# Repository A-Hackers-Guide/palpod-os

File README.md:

# HearthOS

> The software layer of Hearth — a $95k fully-offline luxury home AI and media
> server. This repository provides the orchestration scaffolding: everything a
> single Jetson AGX Orin dev kit needs to boot into a working Pod after one
> `install.sh`.

---

## What this is

HearthOS is the **base platform**. It brings up:

- Media services (Plex, Jellyfin, Audiobookshelf)
- Live-TV proxy (xTeVe → M3U/EPG into Plex & Jellyfin as first-class channels)
- Game & desktop streaming (Sunshine, GPU-accelerated, Moonlight-compatible)
- Headless Steam (Steam Big Picture streamed to any Moonlight client — never to
  the Sphere face)
- Remote Desktop — RustDesk self-hosted (rendezvous + relay) so the Pod can
  view and drive your other machines with your permission; AnyDesk is
  available as an opt-in `--profile anydesk` alternative
- A Postgres 16 database for the `pal-web` control app
- A reverse proxy (Traefik) with LAN-local TLS on `*.palpod.local`
- Reference mount points for the three sibling repos:
  `pal-web`, `pal-voice`, `pal-face`

MVP hardware: **one NVIDIA Jetson AGX Orin 64GB Developer Kit** running
Ubuntu 22.04 aarch64.

Production hardware (future): a cluster of 10× Jetson Orin NX + 10× Ryzen
AI 9 HX 370 nodes on TrueNAS SCALE with 5 TB ECC DDR5 and 35 TB NVMe JBOD.
The compose file here is the **development target**; the production target is
TrueNAS's Kubernetes app catalog (see [`docs/ARCHITECTURE.md`](docs/ARCHITECTURE.md)).

---

## Remote Desktop

The Pod can view and drive your other machines — Macs, PCs, iPhones,
Androids — through a self-hosted RustDesk stack. The rendezvous server
(`hbbs`) handles peer discovery and the relay (`hbbr`) forwards traffic when
a direct LAN path isn't available. Both run on the Pod. **No third-party
server ever touches your streams**, and the X25519 keypair used to
authenticate peers is generated during `install.sh` and never leaves the box.

Typical use:

- *"Hey Hearth, show me the office Mac"* → Pod pulls up a live view of that
  machine on the TV you're near (or any Moonlight extender).
- *"Hey Hearth, click the send button on my laptop"* → Pod drives the mouse and
  keyboard on the remote machine — only for devices you've explicitly
  granted **AI control** to.
- The pal-web UI lists every registered device, opens a session, and shows
  session history from the `remote_sessions` Postgres table.

### Setup flow

1. Install the RustDesk client on the machine you want to reach
   (macOS, Windows, Linux, iOS, Android — all supported by upstream).
2. On the Pod, run `scripts/pair-remote-device.sh` — it prints a one-time
   pairing token and the Pod's rendezvous address.
3. Paste both into the RustDesk client's "ID Server" field. Approve the
   pairing dialog that pops up in pal-web.
4. The device shows up under **Settings → Remote Devices** in pal-web.

### Permission model

- **Default: view-only.** Voice requests like "show me…" work out of the box
  for any paired device.
- **AI control is opt-in per device.** In pal-web, toggle *Allow AI control*
  on the device card. Without this flag the click/type/scroll endpoints
  return 403 even to an authenticated Pod session.
- **Every session is logged.** Start time, end time, initiator (voice / web
  / API), input events for AI-driven sessions, all recorded in
  `remote_sessions`. Revoke a device from the same page — its auth token is
  destroyed and any live session is torn down.

### AnyDesk alternative

Some users prefer AnyDesk's commercial client. The compose file ships an
AnyDesk service behind a `docker compose` profile, disabled by default.
Opt in with:

```bash
docker compose --profile anydesk up -d
```

You'll be prompted to accept the AnyDesk EULA on first launch. RustDesk and
AnyDesk can run side-by-side; pal-web treats them as two backends behind the
same "Remote Devices" list.

---

## Install (Ubuntu 22.04, Jetson AGX Orin)

```bash
git clone https://github.com/palpod/palpod-os.git
cd palpod-os
./install.sh
```

`install.sh` will:

1. Detect the NVIDIA GPU and install the NVIDIA Container Toolkit.
2. Install Docker Engine and the `docker compose` plugin.
3. Copy `.env.example` → `.env` and prompt you for the missing values.
4. Pull every image referenced in `docker-compose.yml`.
5. Run `scripts/first-boot.sh` to create ZFS datasets (if TrueNAS is present)
   or plain directories under `/var/lib/palpod` (Ubuntu default).
6. `docker compose up -d` — and print the URLs to open in your browser.

---

## Architecture

```mermaid
flowchart LR
    subgraph LAN["Home LAN — nothing leaves the house"]
        subgraph Pod["Hearth (Jetson AGX Orin, MVP)"]
            direction TB
            Traefik["Traefik<br/>TLS + subdomains"]
            subgraph Media["Media Stack"]
                Plex
                Jellyfin
                ABS["Audiobookshelf"]
                xTeVe
            end
            subgraph Streaming["Game/Desktop Streaming"]
                Sunshine
                Steam["Headless Steam"]
            end
            subgraph Custom["Custom Hearth services (sibling repos)"]
                PalWeb["pal-web<br/>(unified control app)"]
                PalVoice["pal-voice<br/>(LLM + STT + TTS + wake)"]
                PalFace["pal-face<br/>(Pygame Sphere face)"]
            end
            Postgres[(Postgres 16)]
            PalWeb --> Postgres
            PalVoice --> Postgres
            Traefik --> Plex
            Traefik --> Jellyfin
            Traefik --> ABS
            Traefik --> PalWeb
            xTeVe -.M3U/EPG.-> Plex
            xTeVe -.M3U/EPG.-> Jellyfin
            Steam --Big Picture--> Sunshine
        end
        Moonlight["Moonlight clients<br/>(TV, tablet, phone)"]
        Sphere["Sphere face display<br/>(HDMI-attached)"]
        Extender1["Extender node<br/>(Ryzen AI or Orin NX)"]
        Sunshine <---> Moonlight
        PalFace --HDMI--> Sphere
        Pod <-.mDNS pairing.-> Extender1
    end
```

## Service ports

| Service          | Container         | LAN URL (via Traefik)              | Direct port  | Notes                             |
|------------------|-------------------|------------------------------------|--------------|-----------------------------------|
| Plex             | `plex`            | `https://plex.palpod.local`        | `32400`      | Owner claim token needed on init  |
| Jellyfin         | `jellyfin`        | `https://jelly.palpod.local`       | `8096`       | HW transcode via `/dev/nvhost*`   |
| Audiobookshelf   | `audiobookshelf`  | `https://books.palpod.local`       | `13378`      |                                   |
| xTeVe            | `xteve`           | `https://xteve.palpod.local`       | `34400`      | Feeds Plex & Jellyfin             |
| Sunshine         | `sunshine`        | `https://sunshine.palpod.local`    | `47990`      | Web UI. Stream on 47984–48010     |
| Steam (headless) | `steam-headless`  | (via Sunshine)                     | n/a          | Never routed to Sphere            |
| Postgres 16      | `postgres`        | (internal only)                    | `5432`       | Backing store for `pal-web`       |
| Traefik          | `traefik`         | `https://traefik.palpod.local`     | `80/443`     | Dashboard on `:8080` (internal)   |
| pal-web          | `pal-web`         | `https://pod.palpod.local`         | `3000`       | Sibling repo, code-mounted        |
| pal-voice        | `pal-voice`       | (internal gRPC)                    | `50051`      | Sibling repo, code-mounted        |
| pal-face         | `pal-face`        | (HDMI output, no port)             | n/a          | Sibling repo, code-mounted        |
| RustDesk hbbs    | `rustdesk-hbbs`   | (LAN-direct)                       | `21115-21116`| Rendezvous / ID server            |
| RustDesk hbbr    | `rustdesk-hbbr`   | (LAN-direct)                       | `21117`      | Relay server (fallback path)      |
| AnyDesk (opt-in) | `anydesk`         | (LAN-direct)                       | n/a          | Off by default; `--profile anydesk` |

---

## Known limitations (MVP)

This scaffolding is intentionally opinionated toward the **single-Jetson developer
kit**. In particular:

- **No Kubernetes.** Production Pods run on TrueNAS SCALE and are deployed via
  its Kubernetes app catalog. Porting each service is straightforward but out of
  scope here. See [`docs/ARCHITECTURE.md`](docs/ARCHITECTURE.md) §Production.
- **No ZFS by default.** On Ubuntu, everything lives under `/var/lib/palpod/`.
  If ZFS is detected, the first-boot script will offer to create datasets.
- **No hardware failover.** The compose stack is single-node. Extender pairing
  is defined (see [`docs/EXTENDER_PAIRING.md`](docs/EXTENDER_PAIRING.md)) but
  role reassignment on primary loss is a v1.1 feature.
- **Sunshine + Steam are Linux-native.** On the Jetson (aarch64) Steam runs
  under Proton via Box64 emulation and only a subset of the library is playable.
  Real production nodes use the Ryzen AI x86 servers for gaming.
- **TLS on `*.palpod.local` is a self-signed root** installed on the LAN.
  Public certs are out of scope — nothing here should touch the public internet.

---

## Repo layout

```
palpod-os/
├── docker-compose.yml       # THE compose file
├── install.sh / update.sh / uninstall.sh
├── configs/                 # Per-service config (traefik, xteve, sunshine, …)
├── systemd/                 # Boot units
├── scripts/                 # first-boot, extender-pair, media-import
└── docs/                    # Architecture, install, extender protocol, security, backup
```

## Sibling repos (built in parallel by the other teams)

- `pal-web`   — Next.js unified control app; mounted at `../pal-web`
- `pal-voice` — LLM + Whisper STT + Piper TTS + openWakeWord; mounted at `../pal-voice`
- `pal-face`  — Pygame Sphere face renderer; mounted at `../pal-face`

Update these paths in `.env` if your checkout layout differs.

---

## License

Apache 2.0 — see [LICENSE](LICENSE).

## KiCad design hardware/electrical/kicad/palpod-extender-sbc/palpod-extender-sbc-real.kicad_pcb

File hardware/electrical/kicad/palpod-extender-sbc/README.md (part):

# Hearth Ember SBC - KiCad Project

Thin-client single-board computer for the half-scale Hearth extender: a
Rockchip RK3588 octa-core SoC (quad A76 + quad A55, 6 TOPS NPU) hosts 8 GB
LPDDR5-6400 (Samsung K3LKBFB0EM-MGCP), 128 GB Kingston EMMC128G-M525 eMMC 5.1,
a Realtek RTL8852BE Wi-Fi 6E + BT 5.3 module on M.2 A+E 2230, an RTL8125BG
2.5 GbE PHY, a Cirrus CS43198 stereo DAC feeding a TI TPA3255 315 W class-D
amp for the extender's soundbar + mini-sub, HDMI 2.1 out to the TV, MIPI DSI-2
to the 3.5" levitating orb OLED, USB 3.2 hosts, USB-C 3.2 with PD sink via an
Infineon CYPD3175 (CCG3PA) controller (STM32G071 backup power-seq MCU), and a
Rockchip RK806 companion PMIC for all rails. Also carries a UART link out to
the extender's mini-Halbach controller and a wake-mic pass-through. 8-layer
board, 100 mm x 100 mm, ENIG. See
`../../block-diagrams/extender.md` for the extender-level architecture -
this project is the KiCad implementation of that document for the extender
SBC daughterboard.

## How to open

Requires **KiCad 8.0.0 or later** (KiCad 9 and 10 also open the files cleanly;
we developed and validated against KiCad 10.0.5 on macOS).

```
open -a KiCad /private/tmp/claude-501/-Users-lexer-kindle/80e67baf-6192-4db2-b491-aa5b4ee00c5b/scratchpad/palpod-os/hardware/electrical/kicad/palpod-extender-sbc/palpod-extender-sbc.kicad_pro
```

Or double-click `palpod-extender-sbc.kicad_pro` in Finder. From KiCad's
project manager, open **Schematic Editor** and **PCB Editor**.

The project defines its own project-local symbol and footprint libraries in
`libraries/`; the `sym-lib-table` and `fp-lib-table` files at the project root
register them under the alias `palpod-extender-sbc`. Standard KiCad symbols
(`Device:R`, `Device:C`, `power:*`, `Connector:HDMI_A_Receptacle`,
`Connector:RJ45_MagJack`, `Connector:USB3_A_Receptacle`,
`Connector:USB_C_Receptacle_USB3.2`, `Connector:Barrel_Jack_Switch`,
`Memory_NAND:EMMC128G-M525`, `MCU_ST_STM32G0:STM32G071KBTx`,
`Interface_Ethernet:RTL8125BG`) are embedded in the schematic's
`lib_symbols` block so the schematic opens even if a fresh KiCad install has
not yet had its stock libraries configured; on first save KiCad will link
them back to the real stdlib entries.

## What's populated

- [x] `.kicad_pro` project settings:
    - **8-layer stackup declared in `net_settings` and the PCB itself**:
      F.Cu / In1.Cu = GND1 / In2.Cu = sig1 / In3.Cu = PWR_1V1 /
      In4.Cu = PWR_3V3 / In5.Cu = sig2 / In6.Cu = GND2 / B.Cu.
      1 oz copper outer, 0.5 oz inner, ENIG, ~1.6 mm total thickness.
    - Net classes with impedance targets:
        - `Default`  0.15 mm track / 0.4 mm via
        - `Power`    0.5 mm track / 0.8 mm via, 0.2 mm clearance
        - `USB`      0.11 mm track, 0.13 mm diff gap - **90 R differential** for USB 3.2 SS pairs and USB 2.0 D+/D-
        - `HDMI`     0.14 mm track, 0.15 mm diff gap - **100 R differential**
        - `LPDDR5`   0.09 mm track, 0.10 mm diff gap - **100 R differential + tight length-matching** (fly-by CK, tuned per byte-lane per RK3588 hardware guide)
        - `ETH`      0.15 mm track, 0.15 mm diff gap - 100 R differential for 2.5GbE MDI pairs
    - Auto-assign netclass patterns for `+12V/+5V/+3V3/+1V8/+1V1/+0V9`,
      `USB?_DP/USB?_DN/USBC_*/USB3_*`, `HDMI_TX*/HDMI_CLK*`, `LPDDR5_*`,
      `GMAC_MDI*`.
    - DRC minimums tuned for a proper 8-layer board with fine-pitch BGA fanout
      (0.09 mm min track, 0.3 mm min via, 0.075 mm annular ring, 0.15 mm
      microvia drill available).
- [x] `.kicad_sch` root schematic on A2, populated title block (rev A0,
  2026-08-03), embedded `lib_symbols` for every reference used, including the
  seven custom symbols in the project-local library and the eleven standard
  KiCad references.
- [x] Placed symbols (16 major ICs + connectors + illustrative passives):
    - `U1` RK3588 SoC (huge functional-block symbol with LPDDR5 CH0/CH1,
      HDMI 2.1 TX, MIPI DSI-2, dual USB 3.2, USB-C with SS lanes, PCIe 2.1
      to M.2, GMAC to the GbE PHY, eMMC 5.1, dual I2S, triple UART/I2C, SPI
      to the PMIC, and general-purpose GPIO all broken out as pin groups)
    - `U2` RK806 companion PMIC (10 buck + 7 LDO rail outputs, SPI/PWRON/INT
      to the SoC)
    - `U3` Samsung K3LKBFB0EM-MGCP 8 GB LPDDR5-6400 octa-die
    - `U4` Kingston EMMC128G-M525 128 GB eMMC 5.1
    - `U5` Cirrus CS43198 stereo DAC
    - `U6` TI TPA3255 315 W class-D amp
    - `U7` Realtek RTL8125BG 2.5 GbE PHY
    - `U8` STM32G071KBTx power-sequence / PD-backup MCU
    - `U9` Infineon CYPD3175 (CCG3PA) USB-PD sink controller
    - `M1` Realtek RTL8852BE Wi-Fi 6E + BT 5.3 on an M.2 A+E 2230 socket
    - `J1` HDMI Type-A receptacle (Molex 500254-1927)
    - `J2` RJ45 magjack with integrated transformer + LEDs (Bel L829-1J1T)
    - `J3` USB 3.2 Type-A host receptacle (right edge)
    - `J4` USB 3.2 Type-A host receptacle (left edge)
    - `J5` USB Type-C receptacle (Gen 2 SS + PD sink)
    - `J6` 5.5 x 2.1 mm barrel jack (CUI PJ-063AH) for 12 V input
    - 14x decoupling caps (bulk + local, mix of 10 uF / 100 nF / 220 uF), and
      4x illustrative resistors (HDMI HPD pullups + GbE 49R9 bias).
- [x] Power rail flags (`+12V/+5V/+3V3/+1V8/+1V1/+0V9/GND`) and 20+ pre-placed
  labels (`HDMI_TX0/1_P/N`, `LPDDR5_CH0_DQ0/1`, `USB0_DP/DN`, `USBC_DP/DN`,
  `GMAC_MDIO/MDC`, `EMMC_CLK/CMD`, `I2S0_BCLK/LRCK/SDO/SDI`,
  `UART_HALBACH_TX/RX`, `PMIC_INT_N`) plus 5-6 illustrative wires seeding
  the PMIC rail fanout on the schematic.
- [x] `no_connect` flags on three RK3588 test / reserved pins.
- [x] `libraries/palpod-extender-sbc.kicad_sym` - hand-drawn functional-block
  symbols for the seven specialty ICs (RK3588, RK806, RTL8852BE_M2, CS43198,
  TPA3255, CCG3PA, K3LKBFB0EM). Each is a large rectangular block with pin
  groups and the electrical types marked (`power_in`, `input`, `output`,
  `bidirectional`, `passive`). **The RK3588 and RK806 pin mappings are
  functional-group placeholders; the EE must verify each pin number and name
  against the Rockchip datasheets before wiring.**
- [x] `libraries/palpod-extender-sbc.pretty/` - seven placeholder footprints
  (see `libraries/palpod-extender-sbc.pretty/README.md` for the details and
  per-part verification checklist).
- [x] `.kicad_pcb` - **8-layer stackup declared** (F.Cu / In1.Cu = GND1 /
  In2.Cu = sig1 / In3.Cu = PWR_1V1 / In4.Cu = PWR_3V3 / In5.Cu = sig2 /
  In6.Cu = GND2 / B.Cu), copper thickness 1 oz outer / 0.5 oz inner,
  1.6 mm total, ENIG finish, black soldermask. **100 mm x 100 mm square
  board outline on Edge.Cuts.** Silkscreen title block, layer-stackup note,
  and comment-layer notes about LPDDR5 fly-by / HDMI 100 R / USB 90 R
  differential targets and RK3588 placement plan. 100+ nets pre-declared
  (power rails, HDMI, USB, LPDDR5, ETH, EMMC, I2S, MIPI DSI, etc). No
  footprints placed yet - the EE places them during layout.
- [x] `sym-lib-table` / `fp-lib-table` register the project-local
  `palpod-extender-sbc` library. Standard KiCad libraries are resolved from
  the user's KiCad install.

## What's stubbed / next steps for the EE

- [ ] **Verify placeholder footprints against real datasheets** before
  ordering fab. See `libraries/palpod-extender-sbc.pretty/README.md`. Highest
  risk: the RK3588 FCBGA-948 ball map (real RK3588 has non-uniform depopulated
  regions the placeholder doesn't model), the LPDDR5 FBGA-315 ball map, and
  the RK806 QFN-68 pad layout.
- [ ] **Verify placeholder pin mappings on the custom symbols** against the
  Rockchip RK3588 and RK806 datasheets (both are NDA-gated in places; use the
  Rockchip RK3588 hardware design guide as the primary reference), Cirrus
  CS43198, TI TPA3255, Infineon CCG3PA, Samsung K3LKBFB0EM, and Realtek
  RTL8852BE data sheets. Update the symbol pin numbers/names in
  `libraries/palpod-extender-sbc.kicad_sym` before wiring.
- [ ] Complete the schematic wiring:
    - **LPDDR5** CH0/CH1 fly-by CK + per-byte-lane DQS/DM tuning; ZQ
      terminations; RESET# and CKE topology per RK3588 hardware design guide.
    - **HDMI 2.1** four data pairs + clock pair + CEC + DDC (SCL/SDA) +
      HPD (with 10 k pulldown and ESD/level-shift on 5 V HPD line);
      length-tune to within 5 mm intra-pair, 25 mm inter-pair.
    - **USB 3.2** for each host receptacle: SSTX/SSRX + USB 2.0 D+/D- +
      VBUS with ESD protection (TPD4E02B04 or equivalent), current-limit
      switch, and CC1/CC2 handling (Type-A ports just need Rp).
    - **USB-C 3.2 with PD sink**: CCG3PA handles CC1/CC2 negotiation and
      VBUS pass to the 12 V/5 V rail selection; STM32G071 acts as backup
      power-sequencer if PD negotiation stalls. Mux the USB SS lanes to
      the RK3588's Type-C combo phy.
    - **PCIe 2.1 x1** to the M.2 A+E slot for the RTL8852BE (Wi-Fi/BT).
      Include 100 R diff termination, PERST#/CLKREQ# with pullups, and
      the 100 MHz REFCLK from the RK3588 PCIe PHY.
    - **RGMII / SGMII** from the RK3588 GMAC to the RTL8125BG (choose
      one per datasheet), then MDI0..3 diff pairs into the RJ45 magjack.
      Terminate LED drives at the RJ45's LEDs.
    - **eMMC 5.1** 8-bit bus with DS strobe; add 22 R series termination on
      CLK and CMD; keep DS/CLK length-matched.
    - **I2S** from RK3588 -> CS43198 (data + MCLK + BCLK + LRCK) and a
      separate I2S bus for the wake-mic pass-through header.
    - **TPA3255** BTL wiring for the extender's 4" full-range and 5" sub,
      LC output filters (per TI TIDA-01527), GVDD decoupling, and PBTL vs
      BTL mode select (M1/M2/M3).
    - **PMIC**: RK806 SPI control from RK3588 SPI0, PWRON#/RESETB/SLEEP
      sequencing, per-rail feedback, and 32 kHz RTC crystal.
    - **UART_HALBACH_TX/RX** breakout header (with ESD) to the extender's
      separate mini-Halbach controller board.
    - **Orb** interface: MIPI DSI-2 (4 lanes + clk) to the 3.5" OLED, an
      I2C sidechannel for touch/GPIO, and a 5 V rail with soft-start.
    - **12 V input** protection (TVS + reverse-polarity FET + soft-start
      + eFuse), 12 V -> 5 V buck (~5 A for the amp, ~2 A for the SoC
      subsystem via the PMIC's VSYS).
    - **JTAG + UART** debug headers on the RK3588 test pins and the STM32
      SWD.
- [ ] Run ERC (`kicad-cli sch erc palpod-extender-sbc.kicad_sch` or Tools ->
  Electrical Rules Checker). The current stub generates ~700 violations, all
  consequences of the unwired stubs; drive them to zero.
- [ ] Assign every schematic symbol a valid footprint (Tools -> Assign
  Footprints).
- [ ] Update the PCB from the schematic (Tools -> Update PCB from Schematic
  in the PCB editor).
- [ ] Place footprints on the 100 mm x 100 mm board:
    - RK3588 U1 centered.
    - LPDDR5 U3 on top edge, north of the SoC, oriented for shortest
      byte-lane fanout on In2.Cu (sig1).
    - eMMC U4 south of the SoC.
    - HDMI J1 + USB J3 + RJ45 J2 on the right edge.
    - USB-A J4 + barrel jack J6 + USB-C J5 on the left edge.
    - M.2 M1 on the bottom edge (Wi-Fi antenna clearance).
    - PMIC U2 near the SoC on the left; TPA3255 U6 + CS43198 U5 grouped in
      an analog corner top-right (keep away from LPDDR5 area for EMI).
    - STM32G0 U8 + CCG3PA U9 near the USB-C receptacle.
- [ ] Route USB SS + LPDDR5 differential pairs first (they constrain
  everything). Use the `USB` (90 R diff) and `LPDDR5` (100 R diff) net
  classes.
- [ ] Route HDMI TX0..3 + CLK differential pairs on `HDMI` (100 R diff).
- [ ] Pour GND on In1.Cu and In6.Cu; split In3.Cu into 1.1 V zones (VDD_LOG,
  VDD_CENTER, VDD_DDR); split In4.Cu into 3.3 V zones (VCC3V3_SYS,
  VCC3V3_IO, VCC3V3_AUDIO). Route sig1 (In2.Cu) as the primary LPDDR5 byte-
  lane layer; sig2 (In5.Cu) for HDMI/USB/PCIe.
- [ ] Run DRC to zero.
- [ ] Generate Gerbers + drill + BOM + pick-and-place (`File -> Fabrication
  Outputs`). Cross-check the BOM against `../../block-diagrams/extender.md`.
- [ ] Order 5-unit proto run from JLCPCB (8-layer, ENIG, ~3-week turn).

## Command-line validation

The project has been validated with `kicad-cli` 10.0.5:

```
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
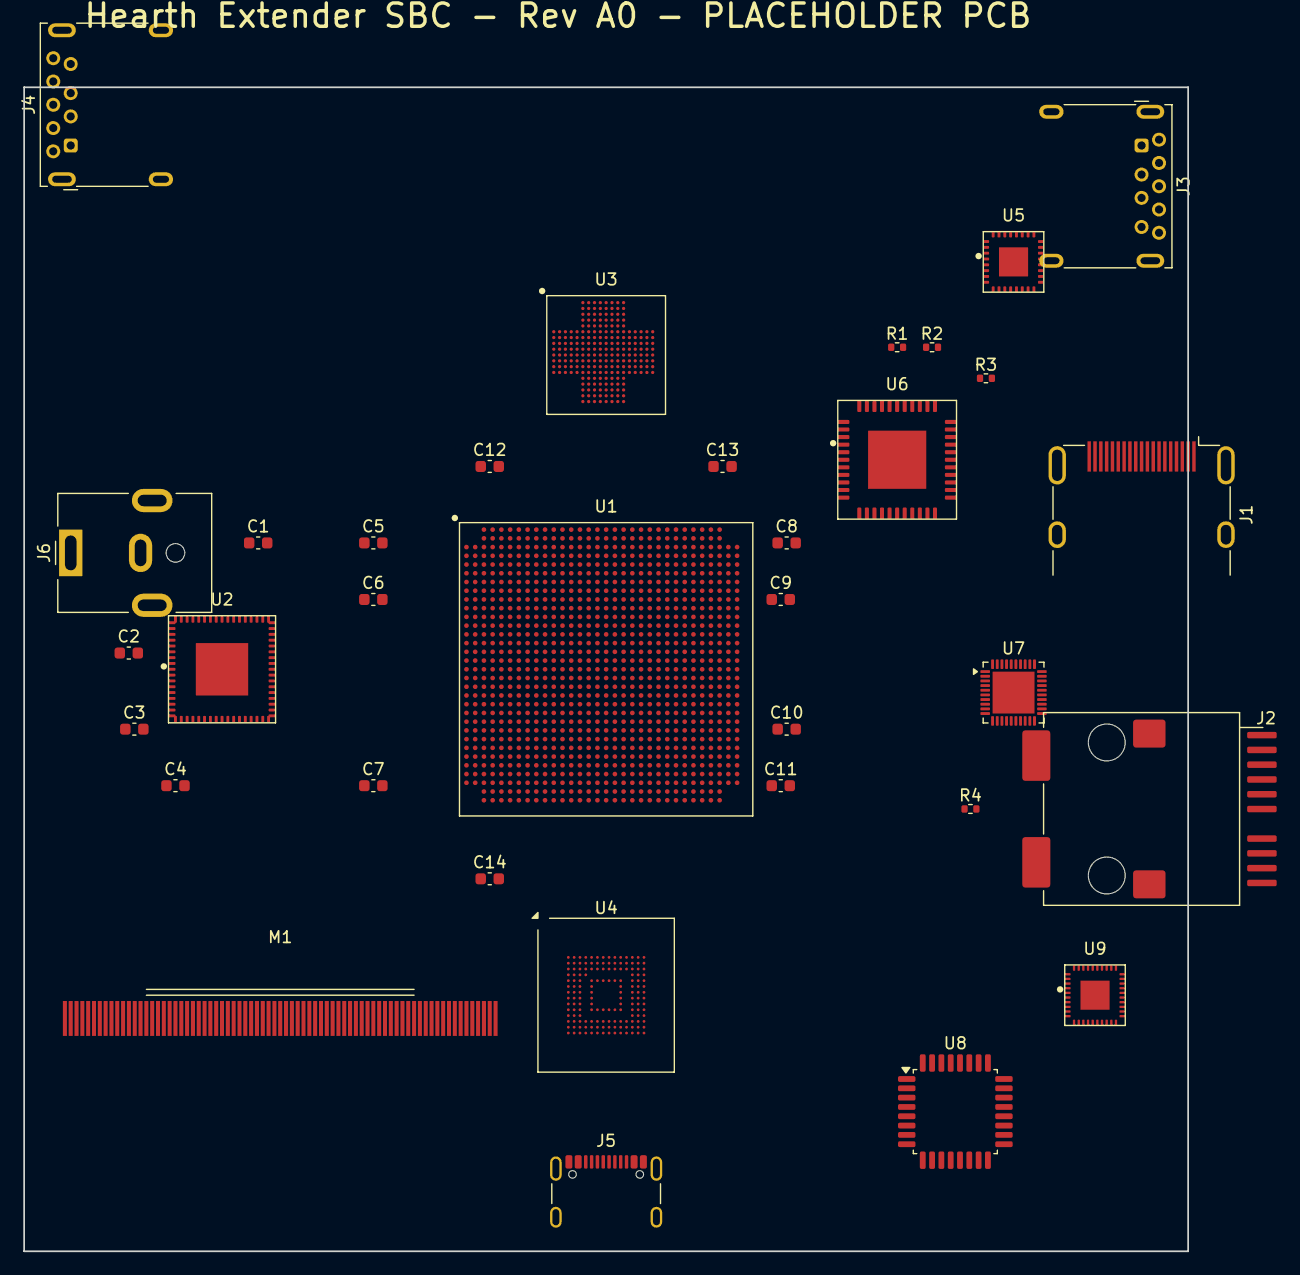
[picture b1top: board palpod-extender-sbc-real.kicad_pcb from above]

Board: 8 copper layers, 100.0 x 100.0 mm, 34 parts (0 on the bottom side), 23 nets, no tracks yet.

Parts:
C1, C3, C5, C9, C11, C13: 10uF; C_0603_1608Metric
C2, C4, C6, C10, C12, C14: 100nF; C_0603_1608Metric
C7, C8: 220uF; C_0603_1608Metric
J1: HDMI_A; HDMI_A_Molex_208658-1001_Horizontal
J2: RJ45_L829; RJ45_Bel_V895-1001-AW_Vertical
J3: USB3_A_1; USB3_A_Molex_48393-001
J4: USB3_A_2; USB3_A_Molex_48393-001
J5: USB_C_3.2; USB_C_Receptacle_GCT_USB4105-xx-A_16P_TopMnt_Horizontal
J6: PJ-063AH; BarrelJack_CUI_PJ-063AH_Horizontal
M1: RTL8852BE_M2; M2_A_E_2230
R1, R2: 10k; R_0402_1005Metric
R3, R4: 49R9; R_0402_1005Metric
U1: RK3588; RK3588_FCBGA948
U2: RK806; RK806_QFN68
U3: K3LKBFB0EM-MGCP; LPDDR5_FBGA315
U4: EMMC128G-M525; LFBGA-153_11.5x13mm_Layout14x14_P0.5mm
U5: CS43198; CS43198_QFN32
U6: TPA3255; TPA3255_HTQFP44
U7: RTL8125BG; QFN-40-1EP_5x5mm_P0.4mm_EP3.6x3.6mm
U8: STM32G071KBTx; LQFP-32_7x7mm_P0.8mm
U9: CYPD3175; CCG3PA_QFN40

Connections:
+0V9: U2.35, U2.37
+1V0: U2.43, U7.1
+1V8: U2.33, U2.38, U2.39, U2.44, U6.7, U7.3
+3V3: M1.36, U2.34, U2.40, U2.41, U5.1, U5.2, U5.3, U6.6, U7.5, U8.1, U8.5, U9.1, U9.2
+5V: J1.18, J3.1, J4.1, J5.A4, J5.B4, U2.1, U2.2, U2.3, U2.4, U2.5, U2.6, U2.7, U2.8, U2.9, U2.10, U2.11, U2.12, U9.4, U9.5
+12V: J6.1, U6.5
CC1: J5.A5, U8.7, U9.16
CC2: J5.B5, U8.8, U9.17
ETH_LED0: J2.9, U7.10
GMAC_MDI0_N: J2.2, U7.16
GMAC_MDI0_P: J2.1, U7.15
GMAC_MDI1_N: J2.6, U7.18
GMAC_MDI1_P: J2.3, U7.17
GND: J1.2, J1.5, J1.8, J1.11, J1.14, J1.17, J2.10, J3.4, J3.7, J4.4, J4.7, J5.A1, J5.A12, J5.B1, J5.B12, J6.2, M1.1, M1.4, M1.35, U2.13, U2.14, U2.15, U2.16, U5.4, U5.5, U6.8, U6.9, U7.2, U8.4, U8.6, U9.7, U9.8
I2C0_SCL: U5.20, U9.12
I2C0_SDA: U5.21, U9.13
MDI_BI_C_N: J2.5, U7.20
MDI_BI_C_P: J2.4, U7.19
MDI_BI_D_N: J2.8, U7.22
MDI_BI_D_P: J2.7, U7.21
SYS_RST_N: U2.22, U5.12, U7.8, U8.3, U9.9
USBC_DN: J5.A7, J5.B7, U9.19
USBC_DP: J5.A6, J5.B6, U9.18

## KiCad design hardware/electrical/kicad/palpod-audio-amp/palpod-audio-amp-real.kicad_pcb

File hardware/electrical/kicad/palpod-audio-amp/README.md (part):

# Hearth Audio Amp - KiCad Project

4-way active amplification board for the Hearth reference-grade audio chain:
tweeter, midrange, woofer, and subwoofer stages, each with its own
Cirrus Logic CS43198 32-bit / 384 kHz DAC feeding a THAT1512 balanced-line
receiver into a Purifi Audio 1ET7040SA Class-D amplifier module. Balanced
I2S / DSD arrives from the DAC master over a Silicon Labs Si8660BB digital
isolator; a Cirrus CS2100-CP fractional-N clock multiplier locks the DAC
master clock. HV rails are +/-60 V from a pair of TI LM5116 controller-based
SMPS stages, sequenced with a TI TPS3808 supervisor. Four Analog Devices
ADT7420 I2C temperature sensors monitor each Purifi module's heatsink.
Speaker outputs land on WBT-0705Cu binding-post terminals with muting relays.
6-layer board, 250 mm x 200 mm rectangle, ENIG, 2 oz outer copper for the
speaker / HV rails. See `../block-diagrams/audio-amp.md` for the
system-level signal chain this project implements.

## How to open

Requires **KiCad 8.0.0 or later** (KiCad 9 and 10 also open the files cleanly;
we developed and validated against KiCad 10.0.5 on macOS).

```
open -a KiCad /private/tmp/claude-501/-Users-lexer-kindle/80e67baf-6192-4db2-b491-aa5b4ee00c5b/scratchpad/palpod-os/hardware/electrical/kicad/palpod-audio-amp/palpod-audio-amp.kicad_pro
```

Or double-click `palpod-audio-amp.kicad_pro` in Finder. From KiCad's project
manager, open **Schematic Editor** and **PCB Editor**.

The project defines its own project-local symbol and footprint libraries in
`libraries/`; the `sym-lib-table` and `fp-lib-table` files at the project root
register them under the alias `palpod-audio-amp`. Standard KiCad symbols
(`Device:R`, `Device:C`, `Device:L`, `power:*`, `Connector:Conn_01x02_Pin`,
`Connector:Conn_01x04_Pin`) are embedded in the schematic's `lib_symbols`
block so the schematic opens even if a fresh KiCad install has not yet had
its stock libraries configured; on first save KiCad will link them back to
the real stdlib entries.

## What's populated

- [x] `.kicad_pro` project settings: **6-layer stackup**, ENIG, HV-friendly minimums (0.2 mm min track / 0.5 mm min copper-to-edge / 0.15 mm min via annular / 0.6 mm min via drill), and 5 net classes:
    - `Default` - 0.25 mm track, 0.6 mm via
    - `I2S_DIFF_100R` - 100 Ohm differential I2S / DSD, 0.2 mm width, 0.15 mm gap
    - `SPKR_HIGH_CURRENT` - 3 mm track, 1.8 mm via (0.5 mm clearance) for speaker outputs
    - `PWR_HV_60V` - 1.5 mm track, 1.2 mm via, 0.8 mm clearance for the +/-60 V bus
    - `ANALOG` - 0.3 mm track, 0.7 mm via for the +/-15 V analog rails
    Auto-assign patterns: `+60V / -60V / VBUS_HV*` -> `PWR_HV_60V`, `SPKR_*` -> `SPKR_HIGH_CURRENT`, `I2S_* / DSD_*` -> `I2S_DIFF_100R`, `AUDIO_* / +15V / -15V` -> `ANALOG`.
- [x] `.kicad_sch` root schematic on A3, populated title block (rev A0, 2026-08-03), embedded `lib_symbols` for every reference used (standard + power + 9 specialty parts).
- [x] Placed symbols (~70 total):
    - 4 x CS43198 DAC (one per channel: TWEETER / MID / WOOFER / SUBWOOFER)
    - 4 x THAT1512 balanced line receiver (per channel)
    - 4 x Purifi 1ET7040SA carrier connector (per channel)
    - 4 x ADT7420 heatsink temperature sensor (per module)
    - 4 x WBT-0705 speaker binding-post terminal (per channel)
    - 1 x Si8660BB digital isolator (I2S input isolation)
    - 1 x CS2100-CP master clock multiplier
    - 2 x LM5116 SMPS controller (one per rail: +60 V and -60 V)
    - 1 x TPS3808 supervisor
    - 24 x 100 nF + 8 x 10 uF decoupling caps + 4 x 1000 uF / 100 V bulk HV caps
    - 8 x 4.7 k pull-ups / gain resistors
    - 2 x 22 uH LM5116 output inductors
    - 1 x 4-pin PSU input connector, 1 x 4-pin I2S / DSD input header
- [x] Illustrative labels + wires seeding the net topology: `+60V / -60V / +15V / -15V / +12V / +5V / +3V3` power rails, `I2S_BCK / I2S_LRCK / I2S_SDIN / DSD_CLK` input bus, `SPKR_{TWEETER,MID,WOOFER,SUB}{+,-}` speaker outputs, `MUTE_* / FAULT_*_N` per-channel control, and `I2C_SCL / I2C_SDA` housekeeping bus.
- [x] `no_connect` flags on four DAC test pins (illustrative).
- [x] `libraries/palpod-audio-amp.kicad_sym` - hand-drawn symbols for the 9 specialty ICs. Each is a rectangular block with functional pin names and grouped pin types (power / input / output / bidirectional / passive). **The CS43198, Purifi, LM5116, and Si8660 pin mappings are placeholder groupings and pin numbers; the EE must verify each pin against the manufacturer datasheet before wiring.**
- [x] `libraries/palpod-audio-amp.pretty/` - 9 placeholder footprints (see `libraries/palpod-audio-amp.pretty/README.md` for the details and per-part verification checklist).
- [x] `.kicad_pcb` - **6-layer stackup declared** (F.Cu / In1.Cu = GND / In2.Cu = PWR_ANA / In3.Cu = PWR_HV / In4.Cu = GND / B.Cu), copper thickness 2 oz outer / 1 oz inner, 1.6 mm total, ENIG finish. **250 mm x 200 mm rectangular board outline drawn on Edge.Cuts.** Silkscreen title block and comment layer notes about the LV / HV isolation moat (3 mm min clearance between domains) and star ground point. No footprints placed yet - the EE places them during layout.
- [x] Pre-declared PCB nets (37) matching the schematic's power rails, I2S / DSD bus, speaker outputs, and control lines.
- [x] `sym-lib-table` / `fp-lib-table` register the project-local `palpod-audio-amp` library. Standard KiCad libraries are resolved from the user's KiCad install.
- [x] `fab/` - pre-generated schematic + PCB PDFs, 6-layer Gerbers, and BOM.csv from `kicad-cli`. All will be re-generated by the EE after real wiring / layout; these are here to prove the project exports end-to-end.

## What's stubbed / next steps for the EE

- [ ] **Verify placeholder footprints against real datasheets** before ordering fab. See `libraries/palpod-audio-amp.pretty/README.md`. In particular the Purifi 1ET7040SA module carrier is a rough 155 x 45 mm rectangle with a single-row 12-pin header; the real module has dual-row terminals on the sides and the exact positions must come from Purifi's datasheet.
- [ ] **Verify placeholder pin mappings on CS43198 / Purifi / LM5116 / Si8660 / CS2100 symbols** against the manufacturer datasheets. Update `libraries/palpod-audio-amp.kicad_sym` with the correct pin numbers, names, and electrical types.
- [ ] Complete the schematic wiring:
    - **I2S / DSD input path**: 4-pin input header -> Si8660BB isolator (VDD1 side) -> per-channel fanout to each CS43198's `SCLK / LRCK / SDIN / MCLK`. Master clock from CS2100 -> Si8660 to distribute to all DACs.
    - **DAC differential output -> line receiver**: CS43198 `AOUTA+/-` and `AOUTB+/-` -> THAT1512 `IN+/-` per channel (+15 V / -15 V rails, low-noise routing).
    - **Line receiver -> Purifi input**: THAT1512 `OUT` -> Purifi carrier connector `IN+ / IN-` (differential drive; add 100 nF DC-blocking cap in series if module requires AC-coupling).
    - **Purifi module power tree**: +60 V and -60 V bus off the two LM5116 stages, star-tied at each module carrier; +12 V aux logic from a linear reg off the +15 V rail.
    - **Speaker output**: Purifi `OUT+ / OUT-` -> mute relay -> WBT-0705 terminal. Add snubber network per Purifi datasheet.
    - **Temperature monitoring**: 4 x ADT7420 on I2C bus with unique address strap; connect to housekeeping MCU (external, not on this board).
    - **Power sequencing**: TPS3808 monitors +60 V readiness; asserts `PWR_GOOD_N` to release Purifi `MUTE` after rails stabilize (soft-start relay optional for turn-on thump control).
    - **HV bulk decoupling**: 4 x 1000 uF / 100 V radials near the Purifi input terminals; add 100 nF X7R film caps in parallel for HF path.
- [ ] Run ERC (`kicad-cli sch erc palpod-audio-amp.kicad_sch` or Tools -> Electrical Rules Checker). The current stub reports 813 violations, all consequences of the unwired stubs; drive them to zero.
- [ ] Assign every schematic symbol a valid footprint (Tools -> Assign Footprints).
- [ ] Update the PCB from the schematic (Tools -> Update PCB from Schematic in the PCB editor).
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
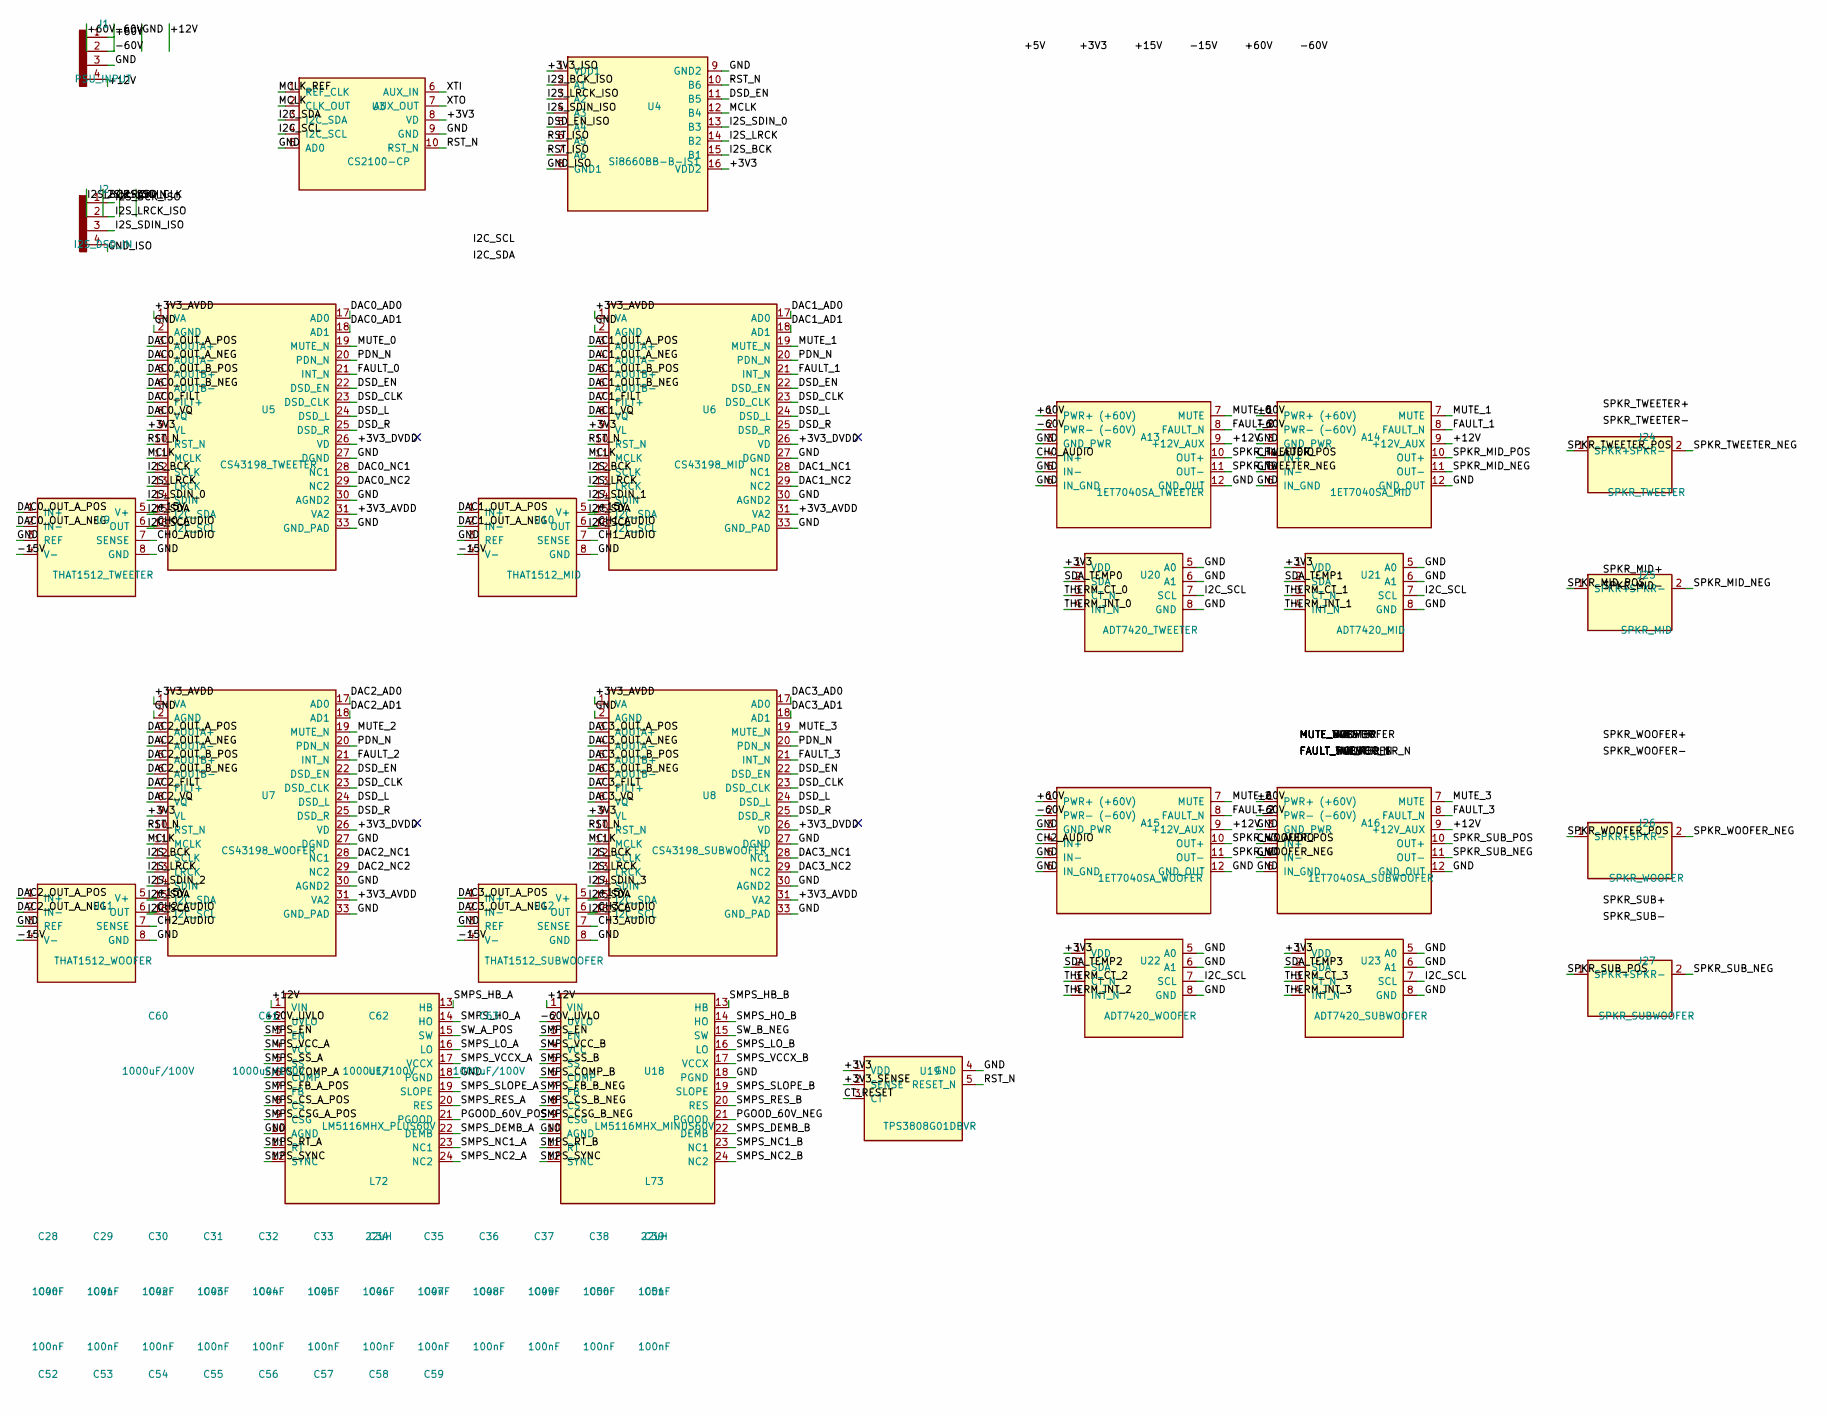
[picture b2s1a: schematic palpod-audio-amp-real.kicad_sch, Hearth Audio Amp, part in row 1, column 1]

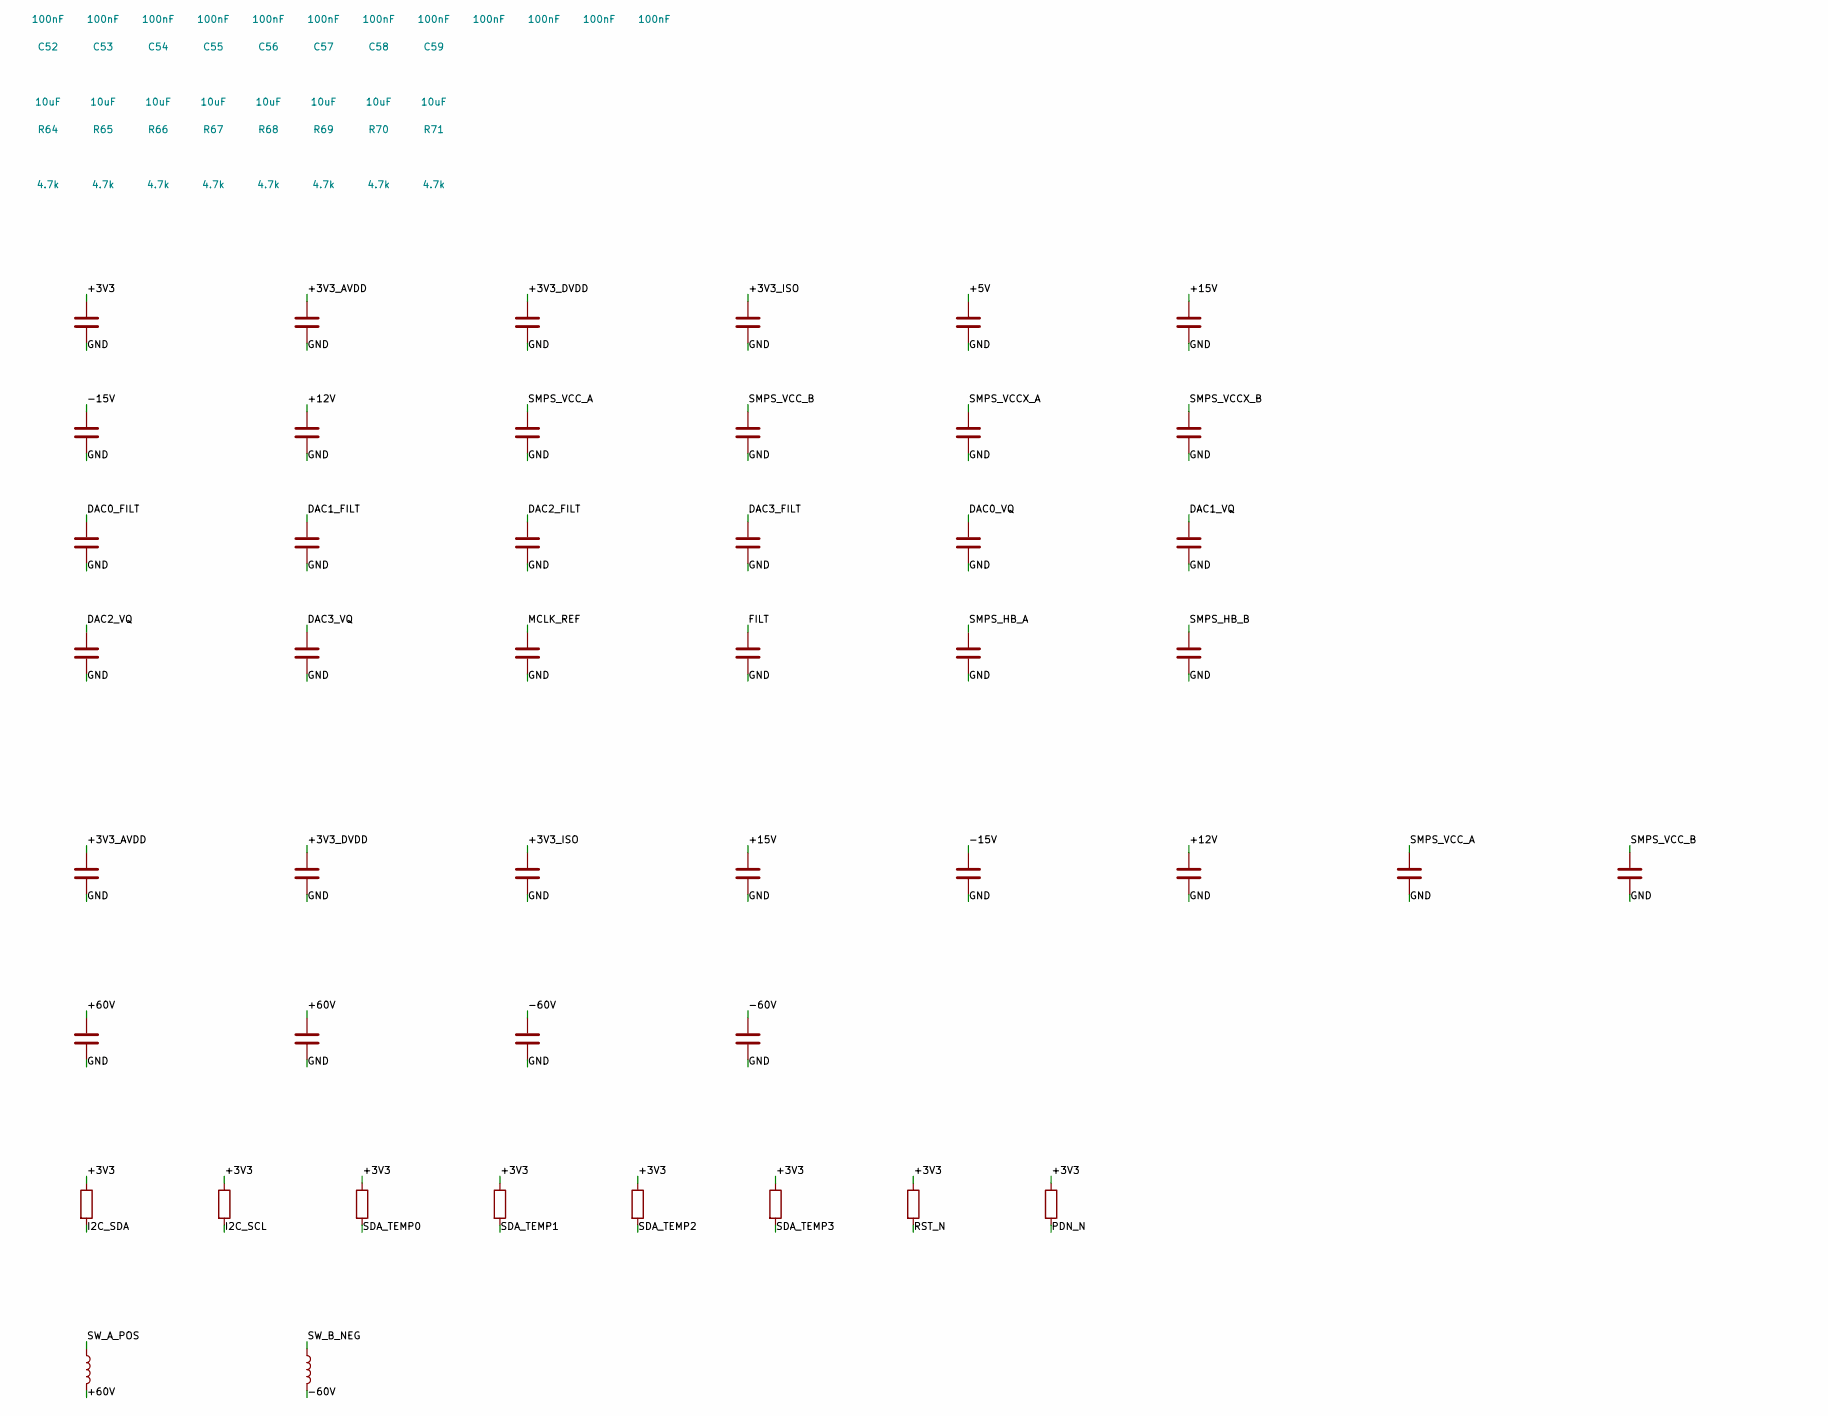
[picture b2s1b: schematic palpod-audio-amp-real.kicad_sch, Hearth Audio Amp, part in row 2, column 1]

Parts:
A13: 1ET7040SA_TWEETER; Purifi_1ET7040SA_Module
A14: 1ET7040SA_MID; Purifi_1ET7040SA_Module
A15: 1ET7040SA_WOOFER; Purifi_1ET7040SA_Module
A16: 1ET7040SA_SUBWOOFER; Purifi_1ET7040SA_Module
C28, C29, C30, C31, C32, C33, C34, C35, C36, C37, C38, C39, C40, C41, C42, C43, C44, C45, C46, C47, C48, C49, C50, C51: 100nF; C_0402_1005Metric
C52, C53, C54, C55, C56, C57, C58, C59: 10uF; C_0805_2012Metric
C60, C61, C62, C63: 1000uF/100V; CP_Radial_D18.0mm_P7.50mm
J1: PSU_INPUT; TerminalBlock_bornier-4_P5.08mm
J2: I2S_DSD_IN; PinHeader_1x04_P2.54mm_Vertical
J24: SPKR_TWEETER; WBT-0705_Terminal
J25: SPKR_MID; WBT-0705_Terminal
J26: SPKR_WOOFER; WBT-0705_Terminal
J27: SPKR_SUBWOOFER; WBT-0705_Terminal
L72, L73: 22uH; L_Coilcraft_XAL1010
R64, R65, R66, R67, R68, R69, R70, R71: 4.7k; R_0402_1005Metric
U3: CS2100-CP; CS2100_MSOP10
U4: Si8660BB-B-IS1; Si8660_SOIC16
U5: CS43198_TWEETER; CS43198_TQFN32
U6: CS43198_MID; CS43198_TQFN32
U7: CS43198_WOOFER; CS43198_TQFN32
U8: CS43198_SUBWOOFER; CS43198_TQFN32
U9: THAT1512_TWEETER; THAT1512_SOIC8
U10: THAT1512_MID; THAT1512_SOIC8
U11: THAT1512_WOOFER; THAT1512_SOIC8
U12: THAT1512_SUBWOOFER; THAT1512_SOIC8
U17: LM5116MHX_PLUS60V; LM5116_HTSSOP24
U18: LM5116MHX_MINUS60V; LM5116_HTSSOP24
U19: TPS3808G01DBVR; TPS3808_SOT23-5
U20: ADT7420_TWEETER; ADT7420_MSOP8
U21: ADT7420_MID; ADT7420_MSOP8
U22: ADT7420_WOOFER; ADT7420_MSOP8
U23: ADT7420_SUBWOOFER; ADT7420_MSOP8

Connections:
+3V3: C28.1, R64.1, R65.1, R66.1, R67.1, R68.1, R69.1, R70.1, R71.1, U3.8 (VD), U4.16 (VDD2), U5.9 (VL), U6.9 (VL), U7.9 (VL), U8.9 (VL), U19.1 (VDD), U20.1 (VDD), U21.1 (VDD), U22.1 (VDD), U23.1 (VDD)
+3V3_AVDD: C29.1, C52.1, U5.1 (VA), U5.31 (VA2), U6.1 (VA), U6.31 (VA2), U7.1 (VA), U7.31 (VA2), U8.1 (VA), U8.31 (VA2)
+3V3_DVDD: C30.1, C53.1, U5.26 (VD), U6.26 (VD), U7.26 (VD), U8.26 (VD)
+3V3_ISO: C31.1, C54.1, U4.1 (VDD1)
+3V3_SENSE: U19.2 (SENSE)
+5V: C32.1
+12V: A13.9 (+12V_AUX), A14.9 (+12V_AUX), A15.9 (+12V_AUX), A16.9 (+12V_AUX), C35.1, C57.1, J1.4, U17.1 (VIN), U18.1 (VIN)
+15V: C33.1, C55.1, U9.5 (V+), U10.5 (V+), U11.5 (V+), U12.5 (V+)
+60V: A13.1 (PWR+ (+60V)), A14.1 (PWR+ (+60V)), A15.1 (PWR+ (+60V)), A16.1 (PWR+ (+60V)), C60.1, C61.1, J1.1, L72.2
+60V_UVLO: U17.2 (UVLO)
-15V: C34.1, C56.1, U9.4 (V-), U10.4 (V-), U11.4 (V-), U12.4 (V-)
-60V: A13.2 (PWR- (-60V)), A14.2 (PWR- (-60V)), A15.2 (PWR- (-60V)), A16.2 (PWR- (-60V)), C62.1, C63.1, J1.2, L73.2
-60V_UVLO: U18.2 (UVLO)
CH0_AUDIO: A13.4 (IN+), U9.6 (OUT), U9.7 (SENSE)
CH1_AUDIO: A14.4 (IN+), U10.6 (OUT), U10.7 (SENSE)
CH2_AUDIO: A15.4 (IN+), U11.6 (OUT), U11.7 (SENSE)
CH3_AUDIO: A16.4 (IN+), U12.6 (OUT), U12.7 (SENSE)
CT_RESET: U19.3 (CT)
DAC0_AD0: U5.17 (AD0)
DAC0_AD1: U5.18 (AD1)
DAC0_FILT: C40.1, U5.7 (FILT+)
DAC0_NC1: U5.28 (NC1)
DAC0_NC2: U5.29 (NC2)
DAC0_OUT_A_NEG: U5.4 (AOUTA-), U9.2 (IN-)
DAC0_OUT_A_POS: U5.3 (AOUTA+), U9.1 (IN+)
DAC0_OUT_B_NEG: U5.6 (AOUTB-)
DAC0_OUT_B_POS: U5.5 (AOUTB+)
DAC0_VQ: C44.1, U5.8 (VQ)
DAC1_AD0: U6.17 (AD0)
DAC1_AD1: U6.18 (AD1)
DAC1_FILT: C41.1, U6.7 (FILT+)
DAC1_NC1: U6.28 (NC1)
DAC1_NC2: U6.29 (NC2)
DAC1_OUT_A_NEG: U6.4 (AOUTA-), U10.2 (IN-)
DAC1_OUT_A_POS: U6.3 (AOUTA+), U10.1 (IN+)
DAC1_OUT_B_NEG: U6.6 (AOUTB-)
DAC1_OUT_B_POS: U6.5 (AOUTB+)
DAC1_VQ: C45.1, U6.8 (VQ)
DAC2_AD0: U7.17 (AD0)
DAC2_AD1: U7.18 (AD1)
DAC2_FILT: C42.1, U7.7 (FILT+)
DAC2_NC1: U7.28 (NC1)
DAC2_NC2: U7.29 (NC2)
DAC2_OUT_A_NEG: U7.4 (AOUTA-), U11.2 (IN-)
DAC2_OUT_A_POS: U7.3 (AOUTA+), U11.1 (IN+)
DAC2_OUT_B_NEG: U7.6 (AOUTB-)
DAC2_OUT_B_POS: U7.5 (AOUTB+)
DAC2_VQ: C46.1, U7.8 (VQ)
DAC3_AD0: U8.17 (AD0)
DAC3_AD1: U8.18 (AD1)
DAC3_FILT: C43.1, U8.7 (FILT+)
DAC3_NC1: U8.28 (NC1)
DAC3_NC2: U8.29 (NC2)
DAC3_OUT_A_NEG: U8.4 (AOUTA-), U12.2 (IN-)
DAC3_OUT_A_POS: U8.3 (AOUTA+), U12.1 (IN+)
DAC3_OUT_B_NEG: U8.6 (AOUTB-)
DAC3_OUT_B_POS: U8.5 (AOUTB+)
DAC3_VQ: C47.1, U8.8 (VQ)
DSD_CLK: U5.23 (DSD_CLK), U6.23 (DSD_CLK), U7.23 (DSD_CLK), U8.23 (DSD_CLK)
DSD_EN: U4.11 (B5), U5.22 (DSD_EN), U6.22 (DSD_EN), U7.22 (DSD_EN), U8.22 (DSD_EN)
DSD_EN_ISO: U4.5 (A4)
DSD_L: U5.24 (DSD_L), U6.24 (DSD_L), U7.24 (DSD_L), U8.24 (DSD_L)
DSD_R: U5.25 (DSD_R), U6.25 (DSD_R), U7.25 (DSD_R), U8.25 (DSD_R)
FAULT_0: A13.8 (FAULT_N), U5.21 (INT_N)
FAULT_1: A14.8 (FAULT_N), U6.21 (INT_N)
FAULT_2: A15.8 (FAULT_N), U7.21 (INT_N)
FAULT_3: A16.8 (FAULT_N), U8.21 (INT_N)
FILT: C49.1
GND: A13.3 (GND_PWR), A13.5 (IN-), A13.6 (IN_GND), A13.12 (GND_OUT), A14.3 (GND_PWR), A14.5 (IN-), A14.6 (IN_GND), A14.12 (GND_OUT), A15.3 (GND_PWR), A15.5 (IN-), A15.6 (IN_GND), A15.12 (GND_OUT), A16.3 (GND_PWR), A16.5 (IN-), A16.6 (IN_GND), A16.12 (GND_OUT), C28.2, C29.2, C30.2, C31.2, C32.2, C33.2, C34.2, C35.2, C36.2, C37.2, C38.2, C39.2, C40.2, C41.2, C42.2, C43.2, C44.2, C45.2, C46.2, C47.2, C48.2, C49.2, C50.2, C51.2, C52.2, C53.2, C54.2, C55.2, C56.2, C57.2, C58.2, C59.2, C60.2, C61.2, C62.2, C63.2, J1.3, U3.5 (AD0), U3.9 (GND), U4.9 (GND2), U5.2 (AGND), U5.27 (DGND), U5.30 (AGND2), U5.33 (GND_PAD), U6.2 (AGND), U6.27 (DGND), U6.30 (AGND2), U6.33 (GND_PAD), U7.2 (AGND), U7.27 (DGND), U7.30 (AGND2), U7.33 (GND_PAD), U8.2 (AGND), U8.27 (DGND), U8.30 (AGND2), U8.33 (GND_PAD), U9.3 (REF), U9.8 (GND), U10.3 (REF), U10.8 (GND), U11.3 (REF), U11.8 (GND), U12.3 (REF), U12.8 (GND), U17.10 (AGND), U17.18 (PGND), U18.10 (AGND), U18.18 (PGND), U19.4 (GND), U20.5 (A0), U20.6 (A1), U20.8 (GND), U21.5 (A0), U21.6 (A1), U21.8 (GND), U22.5 (A0), U22.6 (A1), U22.8 (GND), U23.5 (A0), U23.6 (A1), U23.8 (GND)
GND_ISO: J2.4, U4.8 (GND1)
I2C_SCL: R65.2, U3.4 (I2C_SCL), U5.16 (I2C_SCL), U6.16 (I2C_SCL), U7.16 (I2C_SCL), U8.16 (I2C_SCL), U20.7 (SCL), U21.7 (SCL), U22.7 (SCL), U23.7 (SCL)
I2C_SDA: R64.2, U3.3 (I2C_SDA), U5.15 (I2C_SDA), U6.15 (I2C_SDA), U7.15 (I2C_SDA), U8.15 (I2C_SDA)
I2S_BCK: U4.15 (B1), U5.12 (SCLK), U6.12 (SCLK), U7.12 (SCLK), U8.12 (SCLK)
I2S_BCK_ISO: J2.1, U4.2 (A1)
I2S_LRCK: U4.14 (B2), U5.13 (LRCK), U6.13 (LRCK), U7.13 (LRCK), U8.13 (LRCK)
I2S_LRCK_ISO: J2.2, U4.3 (A2)
I2S_SDIN_0: U4.13 (B3), U5.14 (SDIN)
I2S_SDIN_1: U6.14 (SDIN)
I2S_SDIN_2: U7.14 (SDIN)
I2S_SDIN_3: U8.14 (SDIN)
I2S_SDIN_ISO: J2.3, U4.4 (A3)
MCLK: U3.2 (CLK_OUT), U4.12 (B4), U5.11 (MCLK), U6.11 (MCLK), U7.11 (MCLK), U8.11 (MCLK)
MCLK_REF: C48.1, U3.1 (REF_CLK)
MUTE_0: A13.7 (MUTE), U5.19 (MUTE_N)
MUTE_1: A14.7 (MUTE), U6.19 (MUTE_N)
MUTE_2: A15.7 (MUTE), U7.19 (MUTE_N)
MUTE_3: A16.7 (MUTE), U8.19 (MUTE_N)
PDN_N: R71.2, U5.20 (PDN_N), U6.20 (PDN_N), U7.20 (PDN_N), U8.20 (PDN_N)
PGOOD_60V_NEG: U18.21 (PGOOD)
PGOOD_60V_POS: U17.21 (PGOOD)
RST_ISO: U4.6 (A5), U4.7 (A6)
RST_N: R70.2, U3.10 (RST_N), U4.10 (B6), U5.10 (RST_N), U6.10 (RST_N), U7.10 (RST_N), U8.10 (RST_N), U19.5 (RESET_N)
SDA_TEMP0: R66.2, U20.2 (SDA)
SDA_TEMP1: R67.2, U21.2 (SDA)
SDA_TEMP2: R68.2, U22.2 (SDA)
SDA_TEMP3: R69.2, U23.2 (SDA)
SMPS_COMP_A: U17.6 (COMP)
SMPS_COMP_B: U18.6 (COMP)
SMPS_CSG_A_POS: U17.9 (CSG)
SMPS_CSG_B_NEG: U18.9 (CSG)
SMPS_CS_A_POS: U17.8 (CS)
SMPS_CS_B_NEG: U18.8 (CS)
SMPS_DEMB_A: U17.22 (DEMB)
SMPS_DEMB_B: U18.22 (DEMB)
SMPS_EN: U17.3 (EN), U18.3 (EN)
SMPS_FB_A_POS: U17.7 (FB)
SMPS_FB_B_NEG: U18.7 (FB)
SMPS_HB_A: C50.1, U17.13 (HB)
SMPS_HB_B: C51.1, U18.13 (HB)
SMPS_HO_A: U17.14 (HO)
SMPS_HO_B: U18.14 (HO)
SMPS_LO_A: U17.16 (LO)
SMPS_LO_B: U18.16 (LO)
SMPS_NC1_A: U17.23 (NC1)
SMPS_NC1_B: U18.23 (NC1)
SMPS_NC2_A: U17.24 (NC2)
SMPS_NC2_B: U18.24 (NC2)
SMPS_RES_A: U17.20 (RES)
SMPS_RES_B: U18.20 (RES)
SMPS_RT_A: U17.11 (RT)
SMPS_RT_B: U18.11 (RT)
SMPS_SLOPE_A: U17.19 (SLOPE)
SMPS_SLOPE_B: U18.19 (SLOPE)
SMPS_SS_A: U17.5 (SS)
SMPS_SS_B: U18.5 (SS)
SMPS_SYNC: U17.12 (SYNC), U18.12 (SYNC)
SMPS_VCCX_A: C38.1, U17.17 (VCCX)
SMPS_VCCX_B: C39.1, U18.17 (VCCX)
SMPS_VCC_A: C36.1, C58.1, U17.4 (VCC)
SMPS_VCC_B: C37.1, C59.1, U18.4 (VCC)
SPKR_MID_NEG: A14.11 (OUT-), J25.2 (SPKR-)
SPKR_MID_POS: A14.10 (OUT+), J25.1 (SPKR+)
SPKR_SUB_NEG: A16.11 (OUT-), J27.2 (SPKR-)
SPKR_SUB_POS: A16.10 (OUT+), J27.1 (SPKR+)
SPKR_TWEETER_NEG: A13.11 (OUT-), J24.2 (SPKR-)
SPKR_TWEETER_POS: A13.10 (OUT+), J24.1 (SPKR+)
SPKR_WOOFER_NEG: A15.11 (OUT-), J26.2 (SPKR-)
SPKR_WOOFER_POS: A15.10 (OUT+), J26.1 (SPKR+)
SW_A_POS: L72.1, U17.15 (SW)
SW_B_NEG: L73.1, U18.15 (SW)
THERM_CT_0: U20.3 (CT_N)
THERM_CT_1: U21.3 (CT_N)
THERM_CT_2: U22.3 (CT_N)
THERM_CT_3: U23.3 (CT_N)
THERM_INT_0: U20.4 (INT_N)
THERM_INT_1: U21.4 (INT_N)
THERM_INT_2: U22.4 (INT_N)
THERM_INT_3: U23.4 (INT_N)
XTI: U3.6 (AUX_IN)
XTO: U3.7 (AUX_OUT)
